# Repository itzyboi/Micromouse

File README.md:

# Micromouse
Final year project program

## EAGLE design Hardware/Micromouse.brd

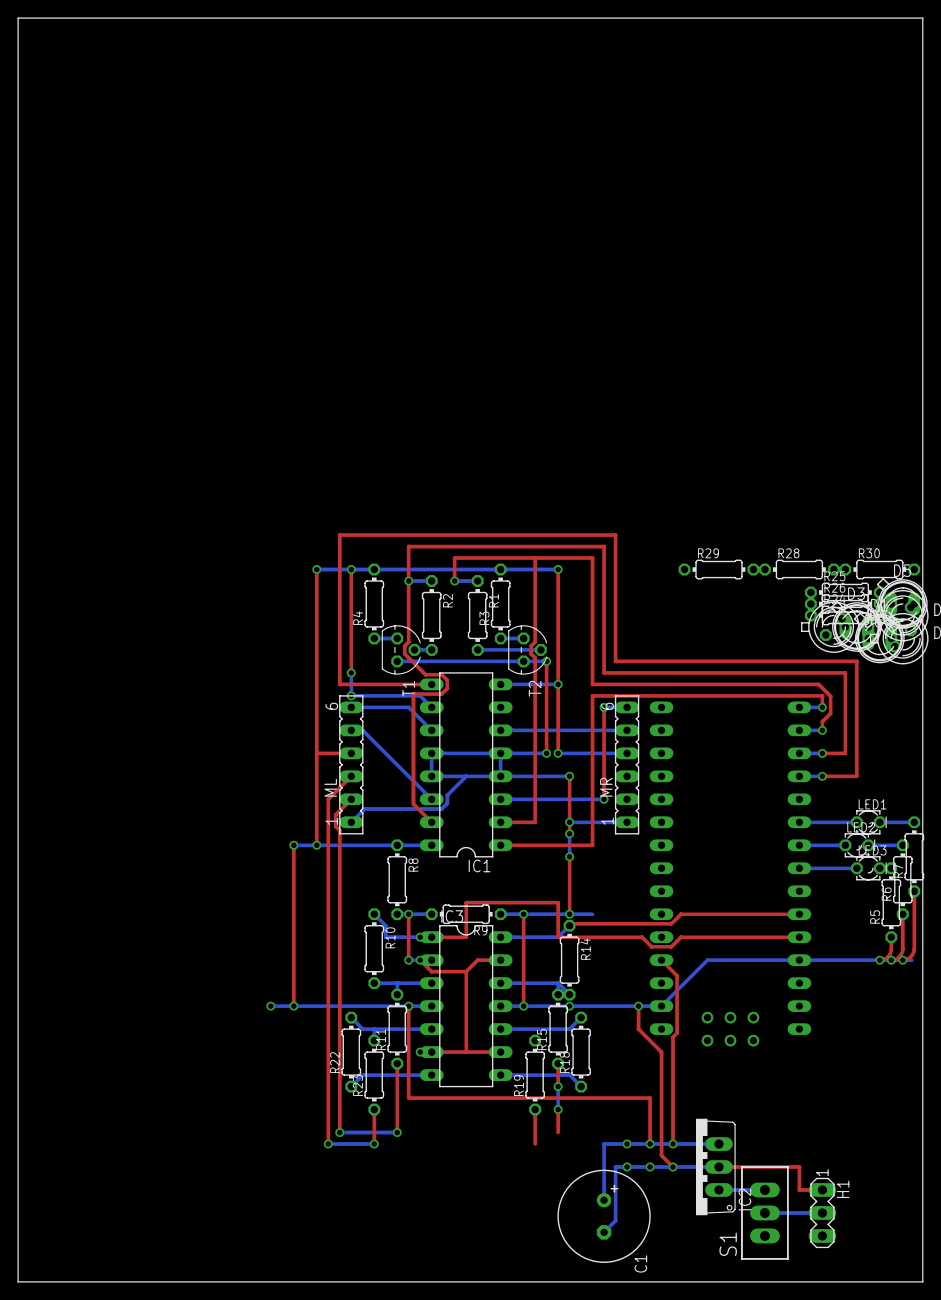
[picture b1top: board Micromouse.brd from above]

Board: 2 copper layers, 100.0 x 139.7 mm, 43 parts (0 on the bottom side), 42 nets.

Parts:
C1: 1000u; E3,5-10
D1, D3, D5: SFH482
D2, D4, D6: BPX65
H1: PWR_Header; MA03-1
IC1: L293D; DIL16
IC2: 7805TV; TO220V
IC3: LM324N; DIL14
LED1, LED2, LED3: LED_LD260
ML: FE06
MR: FE06
R1, R2, R3, R4: 1k; 0204/7
R5, R6, R7: 330; 0204/7
R8: 12K; 0204/7
R9: 2.2k; 0204/7
R10, R14, R18, R22: 220k; 0204/7
R11, R15, R19, R23: 220; 0204/7
R24, R25, R26: 47; 0204/7
R28, R29, R30: 1M; 0204/7
S1: TL32PO; TL3XPO
T1, T2: ZTX451; TO92
U$1: NANO

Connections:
5V: C1.+, D2.K, D4.K, D6.K, IC1.8, IC1.10, IC1.16, IC2.3, IC3.4, ML.4, MR.4, R3.2, R4.2, R8.1, U$1.5V
GND: C1.-, D1.K, D3.K, D5.K, H1.1, IC1.4, IC1.5, IC1.12, IC1.13, IC2.2, IC3.11, ML.1, MR.1, R5.1, R6.1, R7.1, R9.1, R28.1, R29.1, R30.1, T1.1, T2.1, U$1.GND, U$1.GND1
unnamed: IC1.11, ML.6
unnamed: IC1.14, ML.5
unnamed: IC1.3, MR.6
unnamed: IC1.6, MR.5
unnamed: R1.2, T2.2
unnamed: R2.2, T1.2
unnamed: IC1.15, R2.1, U$1.D10
unnamed: IC1.2, R1.1, U$1.D11
unnamed: H1.2, S1.2
unnamed: IC1.1, U$1.D12
unnamed: R3.1, T2.3
unnamed: R4.1, T1.3
unnamed: IC3.7, R22.1
unnamed: LED3.K, R5.2
unnamed: IC1.9, U$1.D9
unnamed: LED2.K, R6.2
unnamed: LED1.K, R7.2
unnamed: IC3.1, R10.1, U$1.D2
unnamed: IC3.3, R10.2, R11.2
unnamed: LED1.A, U$1.D7
unnamed: LED2.A, U$1.D6
unnamed: LED3.A, U$1.D5
unnamed: IC3.2, IC3.6, IC3.9, IC3.13, R8.2, R9.2
unnamed: IC3.8, R18.1
unnamed: ML.2, R11.1
unnamed: ML.3, R23.1
unnamed: IC3.14, R14.1, U$1.D3
unnamed: IC3.12, R14.2, R15.2
unnamed: MR.2, R19.1
unnamed: MR.3, R15.1
unnamed: R24.2, R25.2, R26.2, U$1.D4
unnamed: IC3.10, R18.2, R19.2
unnamed: D4.A, R29.2, U$1.A1
unnamed: D5.A, R26.1
unnamed: IC3.5, R22.2, R23.2
unnamed: D3.A, R25.1
unnamed: D1.A, R24.1
unnamed: D2.A, R28.2, U$1.A2
unnamed: D6.A, R30.2, U$1.A0
VI: IC2.1, S1.3

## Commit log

2016-12-02 Added Arduino file
2016-12-02 Folder reorganisation
    I also tried to start an eagle file
2016-12-29 Schmitt triggers Designed
2017-02-08 Movement functions
    forward x squares, and 90 degree turns (clockwise and anticlockwise) - Untested
    motor encoder interrupt ISRs - untested
2017-03-28 Removed broken ADC attempt + testing
    Program works on board well, just need to tweak the encoder counts definitions at the top properly. Braking maneuvers will probably be removed after next test, as the motor direction switch seems to 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
2017-03-28 Defunct
    Movement program now in Movement.ino
2017-03-29 Rename Movement.ino to Micromouse.ino
    For consistency between branches
2017-03-29 New folder
2017-03-29 Rename test to Micromouse.ino
2017-03-29 Rename Software/Micromouse.ino to Software/Micromouse/Micromouse.ino
2017-03-29 New encoder counter definitions from testing, Testing still needed
2017-03-30 Added testing lines
2017-03-30 -Rewritten functions to now pay attention to both wheels encoders, not just one -Removed braking -New tested values for encoder limits
2017-03-30 Added some kind of control i don't know if it works but it might
2017-04-03 + added for loops to deal with making a maneuver multiple times + added control code to slow motors down when coming up to stop value.(almost eradicated overshoot entirely)
2017-04-03 updated forward left motor pwm value
2017-04-03 Cleanup
2017-04-05 Orientation based turning implemented
2017-04-05 +Sensor setup added +Sensor testing code added
2017-04-06 It works
2017-04-10 More testing of movement needs to be made(Still a bit off, crashes after about 20 squares moved) + DFA works well, need to remove Serial prints + beginning of A* started
2017-04-11 Added A* (plz work)
2017-04-11 Some A* bugs resolved, algorithm worked for short corridor , but not for 6x6 maze check serial out
2017-04-12 A* works, backtracking path does not.
2017-04-12 A* works
    To do
    - Tweak movement params and IR sensor params
2017-04-13 Forward movement fixed to do: tweak anticlockwise a little more it turns slightly too far right now. clockwise looks good but needs more testing.
2017-04-21 Updated hardware + schematic complete + Board almost done but looks a bit terrible
2017-04-25 Comments added
    Added all DFA and main comments, continue from movement section
2017-04-30 Fixed sensor data
2017-05-02 Added serial data
2017-05-03 Added more comments
    Only need to finish commenting AStar()
2018-01-26 Create LICENSE
